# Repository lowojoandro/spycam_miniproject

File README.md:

# ESP32-S3 Spy Camera PCB

This mini project is a custom PCB for a battery powered recording camera using an ESP32-S3.
The download to the files are in the hardware folder. The firmware folder contains the code for the ESP32, camera, buttons, and storage. 

**Note: I did not work on the firmware side yet, partly because I'd like to actually have the PCB first before I start coding.

## Main Requirements

- Camera recording support
- Minimum 480p at 30 FPS
- microSD card storage
- eMMC support
- Start/stop recording button
- Target BOM cost under $25
- Must pass ERC and DRC in KiCad

## Current Design 

- Power input: USB-C
- Battery: Single cell LiPo
- Charger: LiPo charging IC
- Regulator: 3.3 V LDO
- MCU: ESP32-S3-WROOM-1
- Camera: OV2640 camera module (ribbon connected)
- Storage: microSD, optional eMMC footprint
- User controls: reset, boot, start/stop recording

---

## 1. Parts Table 

### Normal Sourcing

This table lists the current PCB components, estimated prices, and target pricing for keeping the project under the $25 goal.
This is NOT using parts sourced from China specifically.

- **Current estimated total:** $43.21
- **Target estimated total:** $16.86

| Ref | Qty | Part / Value | Footprint | Unit Price | Extended | Target Extended | Source |
|---|---:|---|---|---:|---:|---:|---|
| BT1 | 1 | Battery_Cell | Battery:BatteryHolder_Keystone_103_1x20mm | $0.3600 | $0.3600 | $0.3600 |  |
| C1,C2,C4 | 3 | 4u7 | Capacitor_SMD:C_0201_0603Metric | $0.0200 | $0.0600 | $0.0600 | [LCSC](https://www.lcsc.com/category/1142.html) |
| C3,C7,C11,C14,C16 | 5 | 4.7uF | Capacitor_SMD:C_0201_0603Metric | $0.0200 | $0.1000 | $0.1000 | [LCSC](https://www.lcsc.com/category/1142.html) |
| C5,C6 | 2 | 10uF | Capacitor_SMD:C_0201_0603Metric | $0.0300 | $0.0600 | $0.0600 | [LCSC](https://www.lcsc.com/category/1142.html) |
| C8,C9,C10,C12,C13,C15,C18 | 7 | 100nF | Capacitor_SMD:C_0201_0603Metric | $0.0008 | $0.0056 | $0.0056 | [LCSC](https://www.lcsc.com/product-detail/C284966.html) |
| CAM1 | 1 | OV2640 | OV2640:OV2640 | $10.10 | $10.10 | $10.10 | [LCSC](https://www.lcsc.com/product-detail/C359962.html) |
| D1 | 1 | PESD5V0L1ULD | Diode_SMD:D_SOD-882D | $0.0980 | $0.0980 | $0.0980 | [LCSC](https://www.lcsc.com/product-detail/C85380.html) |
| D2 | 1 | LED | LED_SMD:LED_1210_3225Metric | $0.0300 | $0.0300 | $0.0300 | [LCSC](https://www.lcsc.com/category/110.html) |
| J1 | 1 | USB_C_Receptacle_USB2.0_16P | Connector_USB:USB_C_Receptacle_G-Switch_GT-USB-7010ASV | $0.1149 | $0.1149 | $0.1149 | [LCSC](https://www.lcsc.com/category/842.html) |
| J2 | 1 | Micro_SD_Card_Det1 | Connector_Card:microSD_HC_Molex_104031-0811 | $0.6304 | $0.6304 | $0.6304 | [LCSC](https://www.lcsc.com/product-detail/C585350.html) |
| Q1 | 1 | FDN340P | Package_TO_SOT_SMD:SOT-23 | $0.1763 | $0.1763 | $0.1763 | [LCSC](https://www.lcsc.com/product-detail/C75469.html) |
| R1,R2 | 2 | 5000 | Resistor_SMD:R_01005_0402Metric | $0.0200 | $0.0400 | $0.0400 | [Mouser](https://www.mouser.com/c/passive-components/resistors/film-resistors/thick-film-resistors-smd/?case+code+-+in=01005&resistance=10+kOhms) |
| R3 | 1 | 0 | Resistor_SMD:R_0805_2012Metric | $0.0100 | $0.0100 | $0.0100 | [LCSC](https://www.lcsc.com/category/439.html) |
| R4 | 1 | 2k | Resistor_SMD:R_01005_0402Metric | $0.0200 | $0.0200 | $0.0200 | [Mouser](https://www.mouser.com/c/passive-components/resistors/film-resistors/thick-film-resistors-smd/?case+code+-+in=01005&resistance=10+kOhms) |
| R5 | 1 | 470R | Resistor_SMD:R_01005_0402Metric | $0.0200 | $0.0200 | $0.0200 | [Mouser](https://www.mouser.com/c/passive-components/resistors/film-resistors/thick-film-resistors-smd/?case+code+-+in=01005&resistance=10+kOhms) |
| R6 | 1 | 25k | Resistor_SMD:R_01005_0402Metric | $0.0200 | $0.0200 | $0.0200 | [Mouser](https://www.mouser.com/c/passive-components/resistors/film-resistors/thick-film-resistors-smd/?case+code+-+in=01005&resistance=10+kOhms) |
| R7,R9,R10,R11,R12,R13,R14,R15 | 8 | 10k | Resistor_SMD:R_01005_0402Metric | $0.0200 | $0.1600 | $0.1600 | [Mouser](https://www.mouser.com/c/passive-components/resistors/film-resistors/thick-film-resistors-smd/?case+code+-+in=01005&resistance=10+kOhms) |
| R8 | 1 | 100R | Resistor_SMD:R_01005_0402Metric | $0.0200 | $0.0200 | $0.0200 | [Mouser](https://www.mouser.com/c/passive-components/resistors/film-resistors/thick-film-resistors-smd/?case+code+-+in=01005&resistance=10+kOhms) |
| R16,R17 | 2 | 4.7k | Resistor_SMD:R_01005_0402Metric | $0.0200 | $0.0400 | $0.0400 | [Mouser](https://www.mouser.com/c/passive-components/resistors/film-resistors/thick-film-resistors-smd/?case+code+-+in=01005&resistance=10+kOhms) |
| SW1 | 1 | SW_SPST | Button_Switch_SMD:SW_SPST_B3U-1000P-B | $0.1965 | $0.1965 | $0.1965 | [LCSC](https://www.lcsc.com/product-detail/C231329.html) |
| SW2,SW3,SW4 | 3 | SW_Push | Button_Switch_SMD:SW_Push_1P1T_NO_CK_KSC6xxJ | $0.7400 | $2.22 | $0.2112 | [Mouser](https://www.mouser.com/c/electromechanical/switches/tactile-switches/?m=C%26K+Switches&series=KSC6) |
| U1 | 1 | USBLC6-2SC6 | Package_TO_SOT_SMD:SOT-23-6 | $0.1523 | $0.1523 | $0.1523 | [LCSC](https://www.lcsc.com/product-detail/C7519.html) |
| U2 | 1 | MCP73831-2-OT | Package_TO_SOT_SMD:SOT-23-5 | $0.3922 | $0.3922 | $0.3922 | [LCSC](https://www.lcsc.com/product-detail/C424093.html) |
| U3 | 1 | MAX604 | Package_DIP:DIP-5-6_W7.62mm_Socket_LongPads | $8.11 | $8.11 | $0.0895 | [Mouser](https://www.mouser.com/c/semiconductors/power-management-ics/voltage-regulators-voltage-controllers/ldo-voltage-regulators/?series=MAX604) |
| U4 | 1 | ESP32-S3-WROOM-1 | RF_Module:ESP32-S3-WROOM-1 | $3.75 | $3.75 | $3.75 | [LCSC](https://www.lcsc.com/product-detail/C2913199.html) |
| U5 | 1 | EMMC08G-MB29-PM9B | EMMC08G-MB29-PM9B:BGA153N50P14X14_1300X1150X100N | $16.32 | $16.32 | $0.0000 | [Win Source](https://www.win-source.net/products/detail/kingston/emmc08g-mb29-pm9b.html) |

### Sourcing from Shenzhen

Almost all of the low cost parts can be sourced through LCSC.com or similar Chinese electronics suppliers. The target total is lower than the current total because some high cost or optional parts need cheaper substitutes or should be treated as optional, especially the eMMC and regulator.

For less traceable sources, I used a variety of resources to find these alternate parts and where to source them from. For one, this webiste https://www.travelchinaguide.com/cityguides/guangdong/shenzhen-electronics-malls.htm lists the 8 electronics malls in Shenzhen. Huaqiang obviously being the biggest, multiple youtube videos cite what things vendors sell in particular markets. This video from Lady Adafruit covers the book "The Essential Guide to Electronics in Shenzhen", and also describes some parts she was able to buy and where, as well as some useful tips to sourcing the right part.

| Build Option | Estimated Consumed BOM Cost |
|---|---:|
| All parts | $34.45 |
| All parts w/ eMMC optional | $18.13 |
| eMMC optional + AP2112K LDO substitute | $16.41 |

**Note that although total cost is cheap, vendors probably won't sell you individual parts b/c of MOQ. This probably means you'd have to multiply the cheaper parts by 100 (e.g. buying 100 resistors). With MOQ, we can expect up to $100 total.

| Ref | Qty | Value | Suggested Shenzhen Part | Supplier / Part # | Source | Unit Price | BOM Cost | Status |
|---|---:|---|---|---|---|---:|---:|---|
| BT1 | 1 | Battery_Cell | Keystone 103 | C238065 | [LCSC/JLC local China channel](https://www.lcsc.com/product-detail/BatteryConnector_Keystone-103_C238065.html) | $1.08 | $1.08 | Populate |
| C1,C2,C4 | 3 | 4u7 | Murata GRM033R60J475ME05D / JLC equiv. | C3863497 | [JLCPCB SMT assembly](https://jlcpcb.com/partdetail/4431990-GRM033R60J475ME05D/C3863497) | $0.04 | $0.12 | Populate |
| C3,C7,C11,C14,C16 | 5 | 4.7uF | Murata GRM033R60J475ME05D / JLC equiv. | C3863497 | [JLCPCB SMT assembly](https://jlcpcb.com/partdetail/4431990-GRM033R60J475ME05D/C3863497) | $0.04 | $0.20 | Populate |
| C5,C6 | 2 | 10uF | JLC 0201 high-cap MLCC / verify exact PN | C9900079312 / verify | [JLCPCB SMT assembly / consign if needed](https://jlcpcb.com/partdetail/JLCPCBAssembly-BTR02D3/C9900079312) | $0.04 | $0.08 | Populate |
| C8,C9,C10,C12,C13,C15,C18 | 7 | 100nF | FH 0201X104K100NT | C284966 | [LCSC](https://www.lcsc.com/product-detail/C284966.html) | $0.00 | $0.01 | Populate |
| CAM1 | 1 | OV2640 | Waveshare OV2640 Camera Board | C359962 | [LCSC](https://www.lcsc.com/product-detail/C359962.html) | $10.10 | $10.10 | Populate |
| D1 | 1 | PESD5V0L1ULD | LRC LESD8D5.0CAT5G | C172411 | [LCSC alternative](https://www.lcsc.com/product-detail/C172411.html) | $0.01 | $0.01 | Populate |
| D2 | 1 | LED | Vishay SB1210WC01-RG or cheaper local 1210 LED | C6472940 | [LCSC / local HQB bin alternative](https://www.lcsc.com/product-detail/C6472940.html) | $0.31 | $0.31 | Populate |
| J1 | 1 | USB_C_Receptacle_USB2.0_16P | G-Switch GT-USB-7010ASV | C2988369 | [LCSC](https://www.lcsc.com/product-detail/C2988369.html) | $0.08 | $0.08 | Populate |
| J2 | 1 | Micro_SD_Card_Det1 | XKB Connectivity XKTF-015-N | C381082 | [LCSC](https://www.lcsc.com/product-detail/C381082.html) | $0.06 | $0.06 | Populate |
| Q1 | 1 | FDN340P | TECH PUBLIC FDN340P | C2890122 | [LCSC](https://www.lcsc.com/product-detail/mosfets_tech-public-fdn340p_C2890122.html) | $0.06 | $0.06 | Populate |
| R1,R2 | 2 | 5000 | Generic 01005 1% resistor / value match | BOM/RFQ | [LCSC RFQ / local reels](https://www.lcsc.com/product-detail/C2889342.html) | $0.00 | $0.01 | Populate |
| R3 | 1 | 0 | YAGEO/UNI-ROYAL 0R 0805 | BOM/RFQ | [LCSC / local reels](https://www.lcsc.com/category/1199.html) | $0.00 | $0.00 | Populate |
| R4 | 1 | 2k | Generic 01005 1% resistor / value match | BOM/RFQ | [LCSC RFQ / local reels](https://www.lcsc.com/product-detail/C2889342.html) | $0.00 | $0.00 | Populate |
| R5 | 1 | 470R | Generic 01005 1% resistor / value match | BOM/RFQ | [LCSC RFQ / local reels](https://www.lcsc.com/product-detail/C2889342.html) | $0.00 | $0.00 | Populate |
| R6 | 1 | 25k | Generic 01005 1% resistor / value match | BOM/RFQ | [LCSC RFQ / local reels](https://www.lcsc.com/product-detail/C2889342.html) | $0.00 | $0.00 | Populate |
| R7,R9,R10,R11,R12,R13,R14,R15 | 8 | 10k | VO 0402 ±1% 10K / 01005 RFQ if keeping footprint | C2889342 / RFQ | [LCSC / RFQ](https://www.lcsc.com/product-detail/C2889342.html) | $0.00 | $0.01 | Populate |
| R8 | 1 | 100R | Generic 01005 1% resistor / value match | BOM/RFQ | [LCSC RFQ / local reels](https://www.lcsc.com/category/1199.html) | $0.00 | $0.00 | Populate |
| R16,R17 | 2 | 4.7k | Generic 01005 1% resistor / value match | BOM/RFQ | [LCSC RFQ / local reels](https://www.lcsc.com/category/1199.html) | $0.00 | $0.01 | Populate |
| SW1 | 1 | SW_SPST | OMRON B3U-1000P | C231329 | [LCSC/JLCPCB](https://www.lcsc.com/product-detail/C231329.html) | $0.20 | $0.20 | Populate |
| SW2,SW3,SW4 | 3 | SW_Push | CAX TS3425PA-3x4x2.5-160 | C51927438 | [LCSC](https://www.lcsc.com/product-detail/C51927438.html) | $0.04 | $0.13 | Populate |
| U1 | 1 | USBLC6-2SC6 | TECH PUBLIC USBLC6-2SC6 | C2827654 | [LCSC](https://www.lcsc.com/product-detail/C2827654.html) | $0.04 | $0.04 | Populate |
| U2 | 1 | MCP73831-2-OT | Microchip MCP73831T-2ACI/OT | C424093 | [LCSC](https://www.lcsc.com/product-detail/C424093.html) | $0.39 | $0.39 | Populate |
| U3 | 1 | MAX604 | MAX604ESA+T / MAX604CSA+T from Alibaba, or AP2112K-3.3TRG1 substitute | Alibaba / C51118 | [Alibaba Shenzhen seller / LCSC substitute](https://m.alibaba.com/showroom/max604esa--t.html) | $1.88 | $1.88 | Populate |
| U4 | 1 | ESP32-S3-WROOM-1 | ESP32-S3-WROOM-1-N8R8 | C2913201 | [LCSC](https://www.lcsc.com/product-detail/C2913201.html) | $3.36 | $3.36 | Populate |
| U5 | 1 | EMMC08G-MB29-PM9B | Kingston EMMC08G-MB29-PM9B exact; Kioxia THGBMNG5D1LBAIL alt | Win-Source / C391255 | [Win-Source / LCSC alternative](https://www.win-source.net/products/detail/kingston/emmc08g-mb29-pm9b.html) | $16.32 | $16.32 | DNP / optional footprint |

---

## 2. Block Diagram

This block diagram represents the major systems of this PCB. The power comes in as 5v into USB-C, which goes into a LiPo battery charging module. At that point, voltage drops to around a nominal value of 3.7V because of the MCP. This circuit is one way and therefore USB-C only charges the battery, not powering the ESP. The LiPo battery is rated to output around 3.7V, and is then passed through a 3.3V voltage regulator. I used the MAX604 LPO, which I'll explain later. The ESP32-S3-WROOM1 is the main controller which will operate fine from ~2.9-3.3V at 500mA. 

This PCB has two means of storage: A MicroSD, or eMMC. To keep the SD card separate from the BOM, I just used a MicroSD card detector. To keep the eMMC separate from the BOM, I used a custom eMMC footprint that I found off SnapMagic.

For the camera module, I went with the OV2640 because it was the easiest camera to work with. It operatres fine under ~1.7V-3.3V which is what we expect to be at. The camera also supports 800×600 at 30 FPS, which is already much better than the requirements. 

Finally, we have three push switches for start/stop recording, boot, and reset.

---

## 3. Schematic Design

Here are some youtube videos that I used to help along:

-https://www.youtube.com/watch?v=-iZbwzr0dS8
-https://www.youtube.com/shorts/hBdJ9uH2Yd4
-https://www.youtube.com/watch?v=GRd9uTwg7r4
-https://www.youtube.com/watch?v=S24RvYZWYUQ
-https://www.youtube.com/watch?v=g40tUdjZ-Sk
-https://www.youtube.com/watch?v=POPvclRAKOQ
-https://www.youtube.com/watch?v=Ah65M31v87c

### Full View of Schematic

## ERC Passing

## 4. Schematic Breakdown

### USB-C Power Entry

I use 5k resistors as pull down for CC1 and CC2 per the datasheet. I use a USBC connector to protect the data lines and route it to D- and D+. The diode I use has a clamping voltage of 12v, so under normal 5v operations it doesn't activate, but in cases of voltage spikes, it'll short to ground. I use 4.7uF capacitors for decoupling per the datasheet. This is a recurring value throughout the pcb. 

### LiPo Charger / Connector

For LiPo charger, the MCP73 is preferable because it operates at 4.2V, which gets me closer to the 3.3V when it finally reaches the LDO. Also it takes in 5v input and 400-1000mA, >500mA and 5v. I put a note on R4 because it connect to PROG, which regulates how fast you're charging. The higher the R, the slower it charges. It may be preferable to charge slower to prevent spiking. The LED is there to show charging status. Again, we have decoupling capacitors at the input V and output V. 

### Battery

The battery is a single cell LiPo battery that connects to a single pole, single throw switch for simplicity. The 25k is for protection before entering at nominal voltage 3.7V. Then, we have a MOSFET which is controlled by the SPST switch. t takes in 5v input and 400-1000mA, and is a lipo charger. So it basically meets what we need which is >500mA and 5v. 

### 3.3V LDO

You could go a lot of different routes for the regulator. The goal is to minimize the quiescent current and also the low dropout. The TPS783xx part is commony used to deal with quiescent Current but won't be viable for this pcb. I ended up sticking with the MAX604 because although it has a droupout V of 840V at 400mA, I'll get a Vout of around 2.9-3.0V, assuming our nominal aperage is 500mA, which the ESP32 can still run on (based on reddit posts). The values for the decoupling capacitors are 10uF per the datasheet.

### ESP32-S3-WROOM-1

I chose the S3-WROOM-1 bceause it has enough GPIO pins for the camera and storage connections. It also already has PSRAM and it's own crystal built so I wouldn't need to make one. Note that I dedicate a good portion of pins for the camera module so that it can run 8 bits, fulfilling the 480p 30fps requirement. This leaves very little space for the eMMC and I actually have to pin it on 4 bit mode. I can't use the other pins because they're dedicate for internal operations like booting and UART and such.

### OV2640 Camera

This is the standard camera that most people use for ESP32 projects, but the standard Kicad library didn't have the component. So, I found it on SnapMagic.com and imported it to kicad. The link is here: https://www.snapeda.com/parts/OV2640/Omnivision%20Technologies/view-part/?ref=search&t=OV2640%20camera&ab_test_case=b

It operates at 3.3v, can output lower resolution video modes such as SVGA mode which si 800×600 at 30 FPS, which exceeds the project’s minimum 480p/30 FPS requirement. It also supports compressed output so it's less strenuous on memory. Note the pull down resistors. 

### eMMC

Similar to the camera, kicad didn't have the component, so I used this: https://www.snapeda.com/parts/EMMC08G-MB29-PM9B/Kingston/view-part/?company=N%2FA&amp;welcome=home&amp;ref=search&amp;t=eMMC&amp;ab_test_case=b

There's multiple similar eMMCs but this one in particular seemed to be easier to source. Just as I noted in the schematic, the eMMC is on 4 bit mode because of the lack of GPIO pins. 

### MicroSD detector

This is just a standard MicroSD detector. The footprint used however is Molex one because it seemed to be most common. The most important thing to note here is that I didn't actually wire this component (because lack of pins), effectively prioritizing the eMMC as the storage device. If instead we wanted the SD, then I would just replace the eMMC connections with the SD detector.

### Buttons

The top circuit is the button for the booting process. It connects to EN pin of the ESP32 and has an extra resistor to act as a pull down pin. 
The middle circuit is the button for the manual download as well as reset
The bottom circuit is start/stop button. High is start, low is stop.

## 5. PCB Views

Note: The biggest thing here is that I did not finish applying the routes. Because of this, it does not pass the DRC test yet.

I used 4 layers for this PCB to sort of dedicate each layer to a solid reference plane, which should reduce noise and increase stability. I used this video to help: https://www.youtube.com/watch?v=Z7ycNfVJSJ4

## 6. Manufacturing in Shenzhen

The PCB would be about 149.5mm x 137.0mm or about 5.9in x 5.4in. This is pretty large but this is quite a crude and very unpolished version in terms of
optimizing space, traces, layers, etc. Getting this manufactured in Shenzhen is should be easy. One company, NextPCB, is connected with Shenzhen Huaqiu Intelligent Connectivity, and lists its headquarters in Shenzhen. Seeed Studio Fusion is another Shenzhen based prototyping service that offers PCB manufacturing and PCB assembly as well as making custom parts.

## 7. 3D Printed Casing

Ideally this mini project would be interfaced with a 3D printed casing to finish off the "spy camera" look. But, I did not create the model yet.

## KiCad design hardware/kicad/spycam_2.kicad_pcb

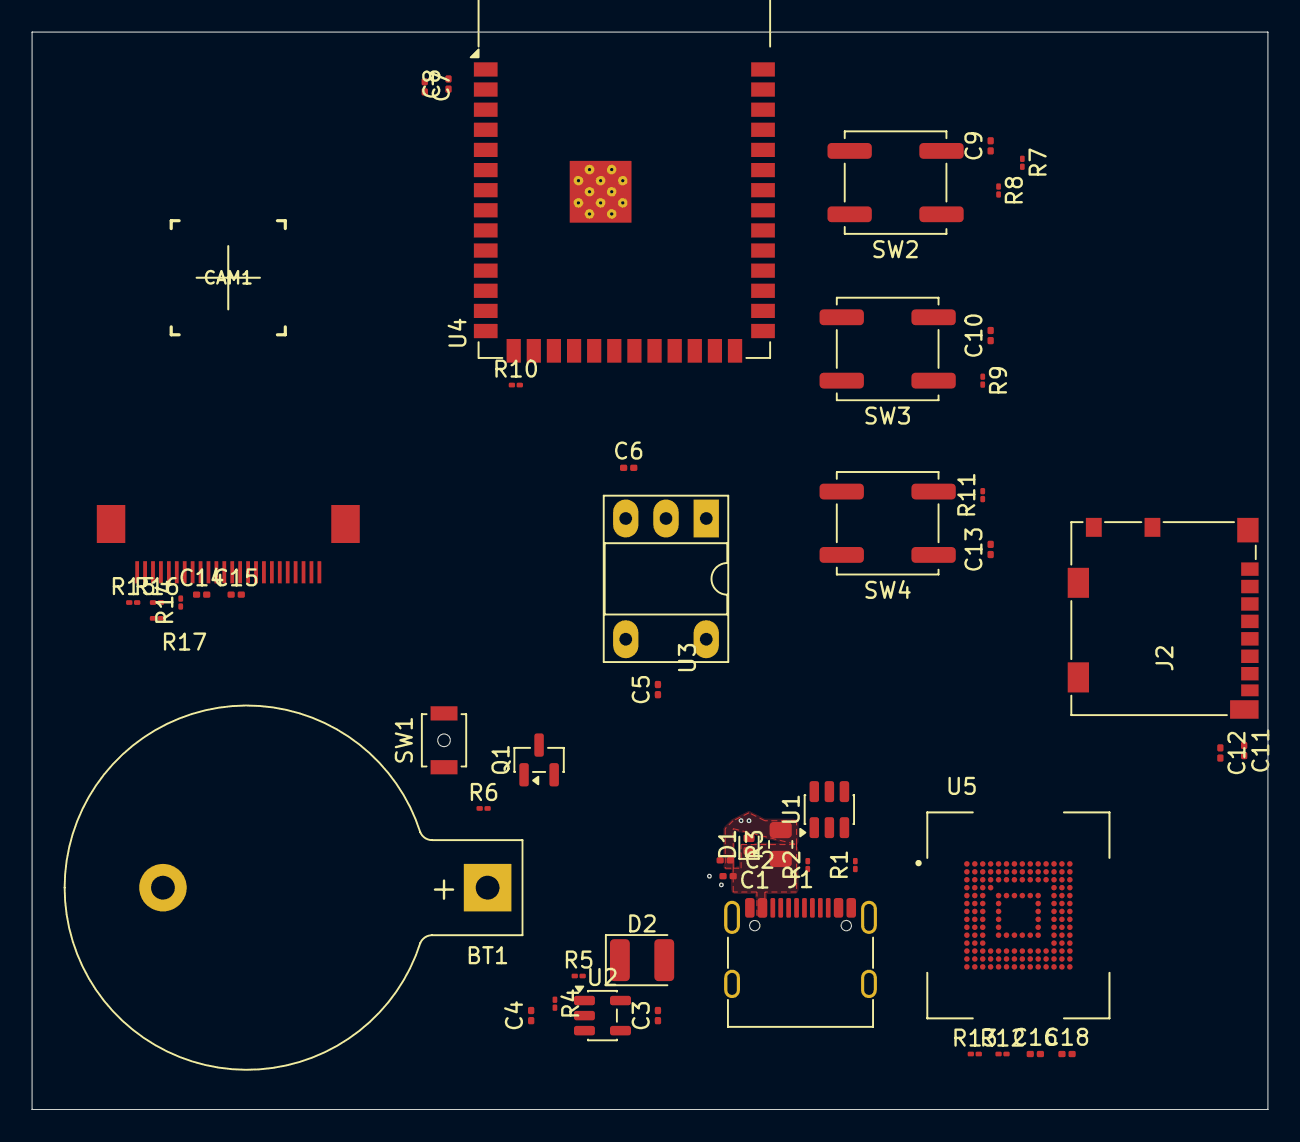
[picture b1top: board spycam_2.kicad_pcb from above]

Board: 4 copper layers, 78.0 x 68.0 mm, 50 parts (0 on the bottom side), 44 nets, no tracks yet.

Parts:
BT1: Battery_Cell; BatteryHolder_Keystone_103_1x20mm
C1, C2, C4: 4u7; C_0201_0603Metric
C3, C7, C11, C14, C16: 4.7uF; C_0201_0603Metric
C5, C6: 10uF; C_0201_0603Metric
C8, C9, C10, C12, C13, C15, C18: 100nF; C_0201_0603Metric
CAM1: OV2640
D1: PESD5V0L1ULD; D_SOD-882D
D2: LED; LED_1210_3225Metric
J1: USB_C_Receptacle_USB2.0_16P; USB_C_Receptacle_G-Switch_GT-USB-7010ASV
J2: Micro_SD_Card_Det1; microSD_HC_Molex_104031-0811
Q1: FDN340P; SOT-23
R1, R2: 5000; R_01005_0402Metric
R3: 0; R_0805_2012Metric
R4: 2k; R_01005_0402Metric
R5: 470R; R_01005_0402Metric
R6: 25k; R_01005_0402Metric
R7, R9, R10, R11, R12, R13, R14, R15: 10k; R_01005_0402Metric
R8: 100R; R_01005_0402Metric
R16, R17: 4.7k; R_01005_0402Metric
SW1: SW_SPST; SW_SPST_B3U-1000P-B
SW2, SW3, SW4: SW_Push; SW_Push_1P1T_NO_CK_KSC6xxJ
U1: USBLC6-2SC6; SOT-23-6
U2: MCP73831-2-OT; SOT-23-5
U3: MAX604; DIP-5-6_W7.62mm_Socket_LongPads
U4: ESP32-S3-WROOM-1
U5: EMMC08G-MB29-PM9B; BGA153N50P14X14_1300X1150X100N

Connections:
+3V3: C6.1, C7.1, C8.1, C11.1, C12.1, C14.1, C15.1, C16.1, C18.1, CAM1.11 (DOVDD), R7.1, R9.1, R10.1, R11.1, R12.1, R13.1, R14.1, R15.1, R16.1, R17.1, U4.2 (3V3), U5.C2 (VDDI)
+5V: C2.1, R3.2
+BATT: BT1.1 (+), C4.1, Q1.2 (S), R6.1, U2.3 (V_{BAT})
+VSW: C5.1, Q1.3 (D), U3.1 (IN), U3.4 (~OFF)
/ESP32-S3/CAM_D0: CAM1.19 (DATA2), U4.4 (IO4)
/ESP32-S3/CAM_D1: CAM1.21 (DATA3), U4.5 (IO5)
/ESP32-S3/CAM_D2: CAM1.22 (DATA4), U4.6 (IO6)
/ESP32-S3/CAM_D3: CAM1.20 (DATA5), U4.7 (IO7)
/ESP32-S3/CAM_D4: CAM1.18 (DATA6), U4.8 (IO15)
/ESP32-S3/CAM_D5: CAM1.16 (DATA7), U4.9 (IO16)
/ESP32-S3/CAM_D6: CAM1.14 (DATA8), U4.10 (IO17)
/ESP32-S3/CAM_D7: CAM1.12 (DATA9), U4.11 (IO18)
/ESP32-S3/CAM_HREF: CAM1.9 (HREF), U4.17 (IO9)
/ESP32-S3/CAM_PCLK: CAM1.17 (PCLK), U4.12 (IO8)
/ESP32-S3/CAM_PDWN: CAM1.8 (PWDN), R14.2, U4.22 (IO14)
/ESP32-S3/CAM_RESET: CAM1.6 (RESET), R15.2, U4.23 (IO21)
/ESP32-S3/CAM_SIOC: CAM1.5 (SIO_C), R17.2, U4.20 (IO12)
/ESP32-S3/CAM_SIOD: CAM1.3 (SIO_D), R16.2, U4.21 (IO13)
/ESP32-S3/CAM_VSYNC: CAM1.7 (VSYNC), U4.18 (IO10), U4.38 (IO2)
/ESP32-S3/CAM_XCLK: CAM1.13 (XCLK), U4.19 (IO11)
/ESP32-S3/D+: J1.A6 (D+), J1.B6 (D+), U1.3 (I/O2)
/ESP32-S3/D-: J1.A7 (D-), J1.B7 (D-), U1.1 (I/O1)
/ESP32-S3/EMMC_CLK: U4.31 (IO38), U5.M6 (CLK)
/ESP32-S3/EMMC_CMD: R13.2, U4.32 (IO39), U5.M5 (CMD)
/ESP32-S3/EMMC_D0: U4.33 (IO40), U5.A3 (DAT0)
/ESP32-S3/EMMC_D1: U4.34 (IO41), U5.A4 (DAT1)
/ESP32-S3/EMMC_D2: U4.35 (IO42), U5.A5 (DAT2)
/ESP32-S3/EMMC_D3: U4.24 (IO47), U5.B2 (DAT3)
/ESP32-S3/EMMC_RST: R12.2, U4.25 (IO48), U5.K5 (~RST)
/ESP32-S3/EN: C9.1, R8.2, U4.3 (EN)
/ESP32-S3/GPIO_0: C10.1, R9.2, SW3.2, U4.27 (IO0)
/ESP32-S3/GPIO_3: R10.2, U4.15 (IO3)
/ESP32-S3/RCD_BTN: C13.1, R11.2, SW4.2
/ESP32-S3/STAT: R5.2, U2.1 (STAT)
/ESP32-S3/USB_D+: U1.4 (I/O2), U4.14 (USB_D+)
/ESP32-S3/USB_D-: U1.6 (I/O1), U4.13 (USB_D-)
GND: BT1.2 (-), C1.2, C2.2, C3.2, C4.2, C5.2, C6.2, C7.2, C8.2, C9.2, C10.2, C11.2, C12.2, C13.2, C14.2, C15.2, C16.2, C18.2, CAM1.2 (AGND), CAM1.15 (DGND), CAM1.MT1 (DGND), CAM1.MT2 (DGND), D1.2 (A), J1.A1 (GND), J1.A12 (GND), J1.B1 (GND), J1.B12 (GND), J1.SH (SHIELD), J2.4 (VDD), J2.6 (VSS), J2.SH (SHIELD), R1.2, R2.2, R4.2, SW1.2 (B), SW2.1, SW3.1, SW4.1, U1.2 (GND), U2.2 (V_{SS}), U3.2 (GND), U3.3 (GND), U3.6 (GND), U4.1 (GND), U4.40 (GND), U4.41 (GND)
unnamed: D2.1 (K), R5.1
unnamed: J1.A5 (CC1), R2.1
unnamed: J1.B5 (CC2), R1.1
unnamed: Q1.1 (G), R6.2, SW1.1 (A)
unnamed: R7.2, R8.1, SW2.2
unnamed: R4.1, U2.5 (PROG)
VBUS: C1.1, C3.1, D1.1 (K), D2.2 (A), J1.A4 (VBUS), J1.A9 (VBUS), J1.B4 (VBUS), J1.B9 (VBUS), R3.1, U2.4 (V_{DD})

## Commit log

2026-05-14 Added README
2026-05-14 Revise README for ESP32-S3 Spy Camera project
    Updated project name and added detailed project requirements and design specifications.
2026-05-14 Update README.md formatting and content
2026-05-14 Enhance README with design details and diagrams
    Added main design blocks, block diagram, and schematic design sections to the README.
2026-05-14 Revise README for ESP32-S3 Spy Camera PCB
    Updated README to enhance clarity and detail about the ESP32-S3 Spy Camera PCB project, including requirements, design, block diagram, and schematic.
2026-05-14 Update README with detailed project specifications
2026-05-14 Update README with project details and components
2026-05-14 Revise README with detailed project specifications
    Updated README to include parts table, sourcing information, and detailed design sections.
2026-05-14 Update print statement from 'Hello' to 'Goodbye'
2026-05-14 Update fmt.Println message from 'Hello' to 'Goodbye'
2026-05-14 changed stuff
2026-05-14 changing stuff
2026-05-14 added changes
